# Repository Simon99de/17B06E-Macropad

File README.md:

# 17B06E-Macropad (by Simon99de)
> [!WARNING]
> Please note: The code is no longer being updated on GitHub!
> 
> The project has been moved to [Codeberg](https://codeberg.org/Simon99de/17B06E-Macropad)!

***
Eine deutsche Anleitung findest du auf meiner Website: [Simon99.de](https://simon99.de/blog/17b06e-macropad/)

It is a simple 4x4 (+1) numpad with 6 rotary encoders, 4x4 RGB LEDs, OLED display, and hot-swap keys.

You can customize all 6 encoders and 17 keys however you want. It also supports multiple layers (/pages), which means that a single key can do much more. (That's why the keyboard has 17 keys instead of 16.)

It can be an alternative to various keyboards such as Streamdeck+, Loupdeck Live, etc. if you don't need the screen behind the keys. In addition, the Macropad keyboard does not require any background software to function, which means increased compatibility.

Powered by QMK via Waveshare RP2040-Plus / Raspberry Pi Pico (1).

### What does 17B06E mean?
I chose the name 17B06E-Macropad because it describes everything the Macropad has. 17 Buttons + 6 Encoders. It also has RGB and a small OLED display.
The top button is used to switch profiles, giving you 16 x 4 (or more/less) buttons at your disposal, with the current profile shown on the display.

***

#### The old code is in the V1 branch.

#### But you should go to Codeberg! (link above)

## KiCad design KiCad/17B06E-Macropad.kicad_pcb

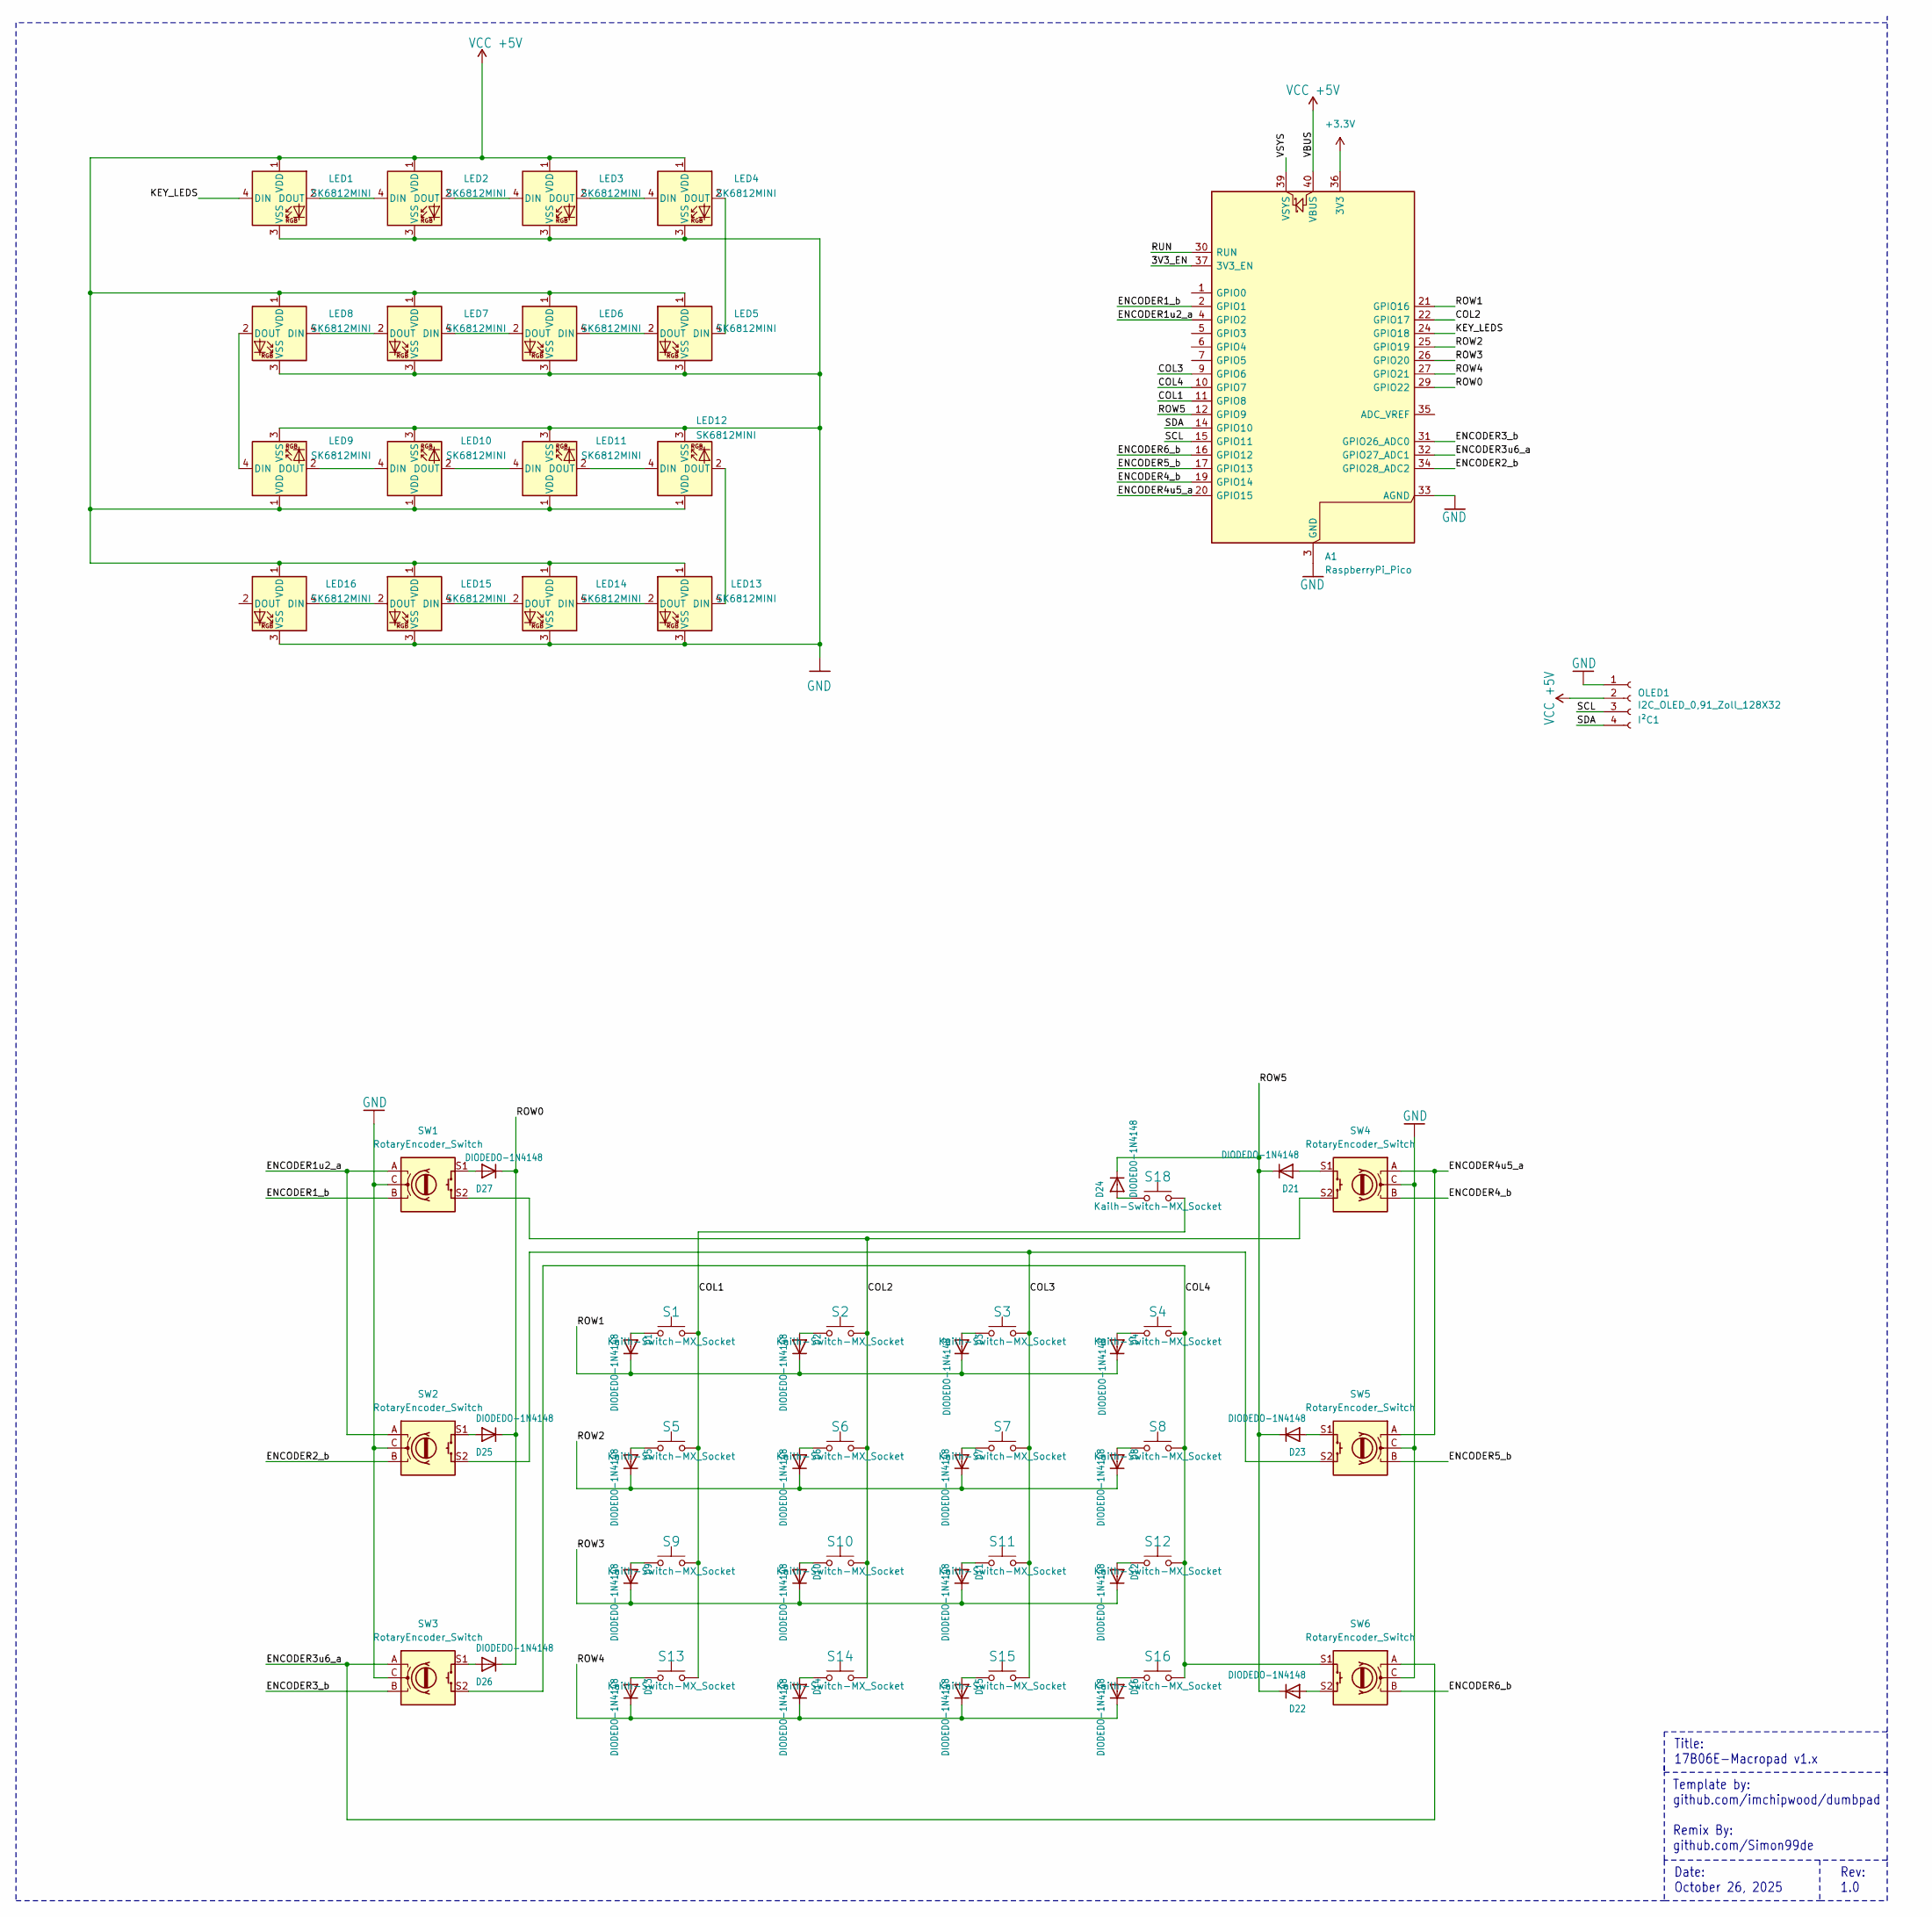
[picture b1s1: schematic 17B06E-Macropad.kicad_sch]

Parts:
A1: RaspberryPi_Pico; RaspberryPi_Pico_No_WIFI
D1, D2, D3, D4, D5, D6, D7, D8, D9, D10, D11, D12, D13, D14, D15, D16, D21, D22, D23, D24, D25, D26, D27: DIODEDO-1N4148; DO-1N4148
LED1, LED2, LED3, LED4, LED5, LED6, LED7, LED8, LED9, LED10, LED11, LED12, LED13, LED14, LED15, LED16: SK6812MINI; YS-SK6812MINI-E
OLED1: I2C_OLED_0,91_Zoll_128X32; OLED
S1, S2, S3, S4, S5, S6, S7, S8, S9, S10, S11, S12, S13, S14, S15, S16, S18: Kailh-Switch-MX_Socket; Kailh-CPG151101S11_MX_Socket-1.00u
SW1, SW2, SW3, SW4, SW5, SW6: RotaryEncoder_Switch; RotaryEncoder_Alps_EC11E-Switch_Vertical_H20mm

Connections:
/COL1: A1.11 (GPIO8), S1.2, S5.2, S9.2, S13.2, S18.2; also elsewhere on the board
/COL2: A1.22 (GPIO17), S2.2, S6.2, S10.2, S14.2, SW1.S2, SW4.S2; also elsewhere on the board
/COL3: A1.9 (GPIO6), S3.2, S7.2, S11.2, S15.2, SW2.S2, SW5.S2; also elsewhere on the board
/COL4: A1.10 (GPIO7), S4.2, S8.2, S12.2, S16.2, SW3.S2, SW6.S1; also elsewhere on the board
/ENCODER1_b: A1.2 (GPIO1), SW1.B; also elsewhere on the board
/ENCODER1u2_a: A1.4 (GPIO2), SW1.A, SW2.A; also elsewhere on the board
/ENCODER2_b: A1.34 (GPIO28_ADC2), SW2.B; also elsewhere on the board
/ENCODER3_b: A1.31 (GPIO26_ADC0), SW3.B; also elsewhere on the board
/ENCODER3u6_a: A1.32 (GPIO27_ADC1), SW3.A, SW6.A; also elsewhere on the board
/ENCODER4_b: A1.19 (GPIO14), SW4.B; also elsewhere on the board
/ENCODER4u5_a: A1.20 (GPIO15), SW4.A, SW5.A; also elsewhere on the board
/ENCODER5_b: A1.17 (GPIO13), SW5.B; also elsewhere on the board
/ENCODER6_b: A1.16 (GPIO12), SW6.B; also elsewhere on the board
/KEY_LEDS: A1.24 (GPIO18), LED1.4 (DIN); also elsewhere on the board
/ROW0: A1.29 (GPIO22), D25.C, D26.C, D27.C; also elsewhere on the board
/ROW1: A1.21 (GPIO16), D1.C, D2.C, D3.C, D4.C; also elsewhere on the board
/ROW2: A1.25 (GPIO19), D5.C, D6.C, D7.C, D8.C; also elsewhere on the board
/ROW3: A1.26 (GPIO20), D9.C, D10.C, D11.C, D12.C; also elsewhere on the board
/ROW4: A1.27 (GPIO21), D13.C, D14.C, D15.C, D16.C; also elsewhere on the board
/ROW5: A1.12 (GPIO9), D21.C, D22.C, D23.C, D24.C; also elsewhere on the board
/SCL: A1.15 (GPIO11), OLED1.3; also elsewhere on the board
/SDA: A1.14 (GPIO10), OLED1.4; also elsewhere on the board
GND: A1.3 (GND), A1.8 (GND), A1.13 (GND), A1.18 (GND), A1.23 (GND), A1.28 (GND), A1.33 (AGND), A1.38 (GND), LED1.3 (VSS), LED2.3 (VSS), LED3.3 (VSS), LED4.3 (VSS), LED5.3 (VSS), LED6.3 (VSS), LED7.3 (VSS), LED8.3 (VSS), LED9.3 (VSS), LED10.3 (VSS), LED11.3 (VSS), LED12.3 (VSS), LED13.3 (VSS), LED14.3 (VSS), LED15.3 (VSS), LED16.3 (VSS), OLED1.1, SW1.C, SW2.C, SW3.C, SW4.C, SW5.C, SW6.C; also elsewhere on the board
unnamed: D1.A, S1.1
unnamed: D2.A, S2.1
unnamed: D3.A, S3.1
unnamed: D4.A, S4.1
unnamed: D5.A, S5.1
unnamed: D6.A, S6.1
unnamed: D7.A, S7.1
unnamed: D8.A, S8.1
unnamed: D9.A, S9.1
unnamed: D10.A, S10.1
unnamed: D11.A, S11.1
unnamed: D12.A, S12.1
unnamed: D13.A, S13.1
unnamed: D14.A, S14.1
unnamed: D15.A, S15.1
unnamed: D16.A, S16.1
unnamed: D21.A, SW4.S1
unnamed: D22.A, SW6.S2
unnamed: D23.A, SW5.S1
unnamed: D24.A, S18.1
unnamed: D25.A, SW2.S1
unnamed: D26.A, SW3.S1
unnamed: D27.A, SW1.S1
unnamed: LED1.2 (DOUT), LED2.4 (DIN)
unnamed: LED2.2 (DOUT), LED3.4 (DIN)
unnamed: LED3.2 (DOUT), LED4.4 (DIN)
unnamed: LED4.2 (DOUT), LED5.4 (DIN)
unnamed: LED5.2 (DOUT), LED6.4 (DIN)
unnamed: LED6.2 (DOUT), LED7.4 (DIN)
unnamed: LED7.2 (DOUT), LED8.4 (DIN)
unnamed: LED8.2 (DOUT), LED9.4 (DIN)
unnamed: LED9.2 (DOUT), LED10.4 (DIN)
unnamed: LED10.2 (DOUT), LED11.4 (DIN)
unnamed: LED11.2 (DOUT), LED12.4 (DIN)
unnamed: LED12.2 (DOUT), LED13.4 (DIN)
unnamed: LED13.2 (DOUT), LED14.4 (DIN)
unnamed: LED14.2 (DOUT), LED15.4 (DIN)
unnamed: LED15.2 (DOUT), LED16.4 (DIN)
VCC +5V: A1.40 (VBUS), LED1.1 (VDD), LED2.1 (VDD), LED3.1 (VDD), LED4.1 (VDD), LED5.1 (VDD), LED6.1 (VDD), LED7.1 (VDD), LED8.1 (VDD), LED9.1 (VDD), LED10.1 (VDD), LED11.1 (VDD), LED12.1 (VDD), LED13.1 (VDD), LED14.1 (VDD), LED15.1 (VDD), LED16.1 (VDD), OLED1.2; also elsewhere on the board

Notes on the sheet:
Rev: 1.0
Template by: github.com/imchipwood/dumbpad Remix By: github.com/Simon99de
Title: 17B06E-Macropad v1.x
Date: October 26, 2025

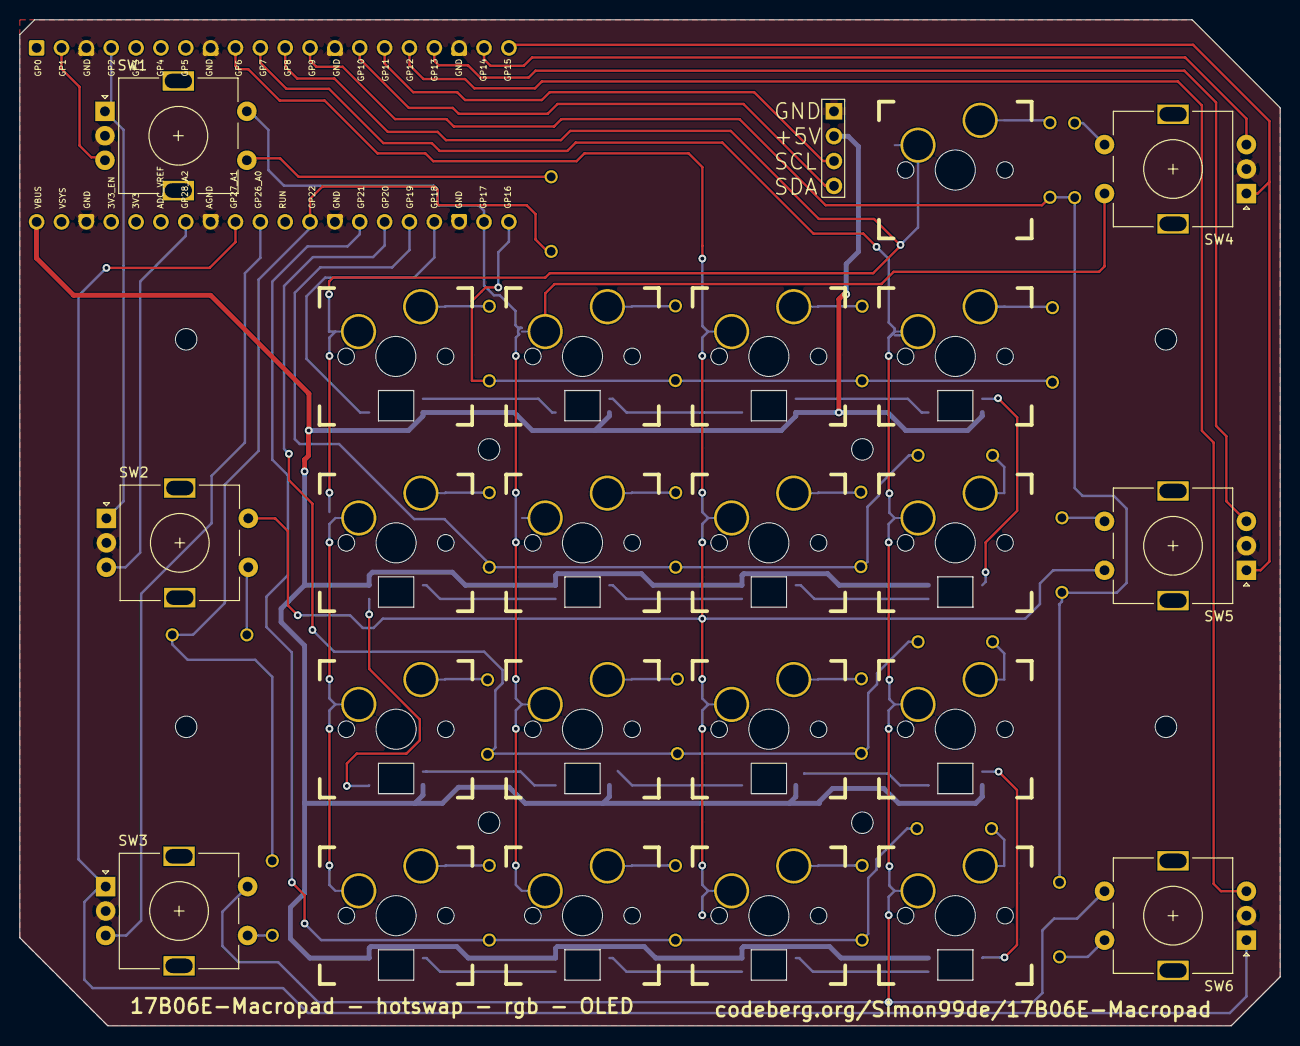
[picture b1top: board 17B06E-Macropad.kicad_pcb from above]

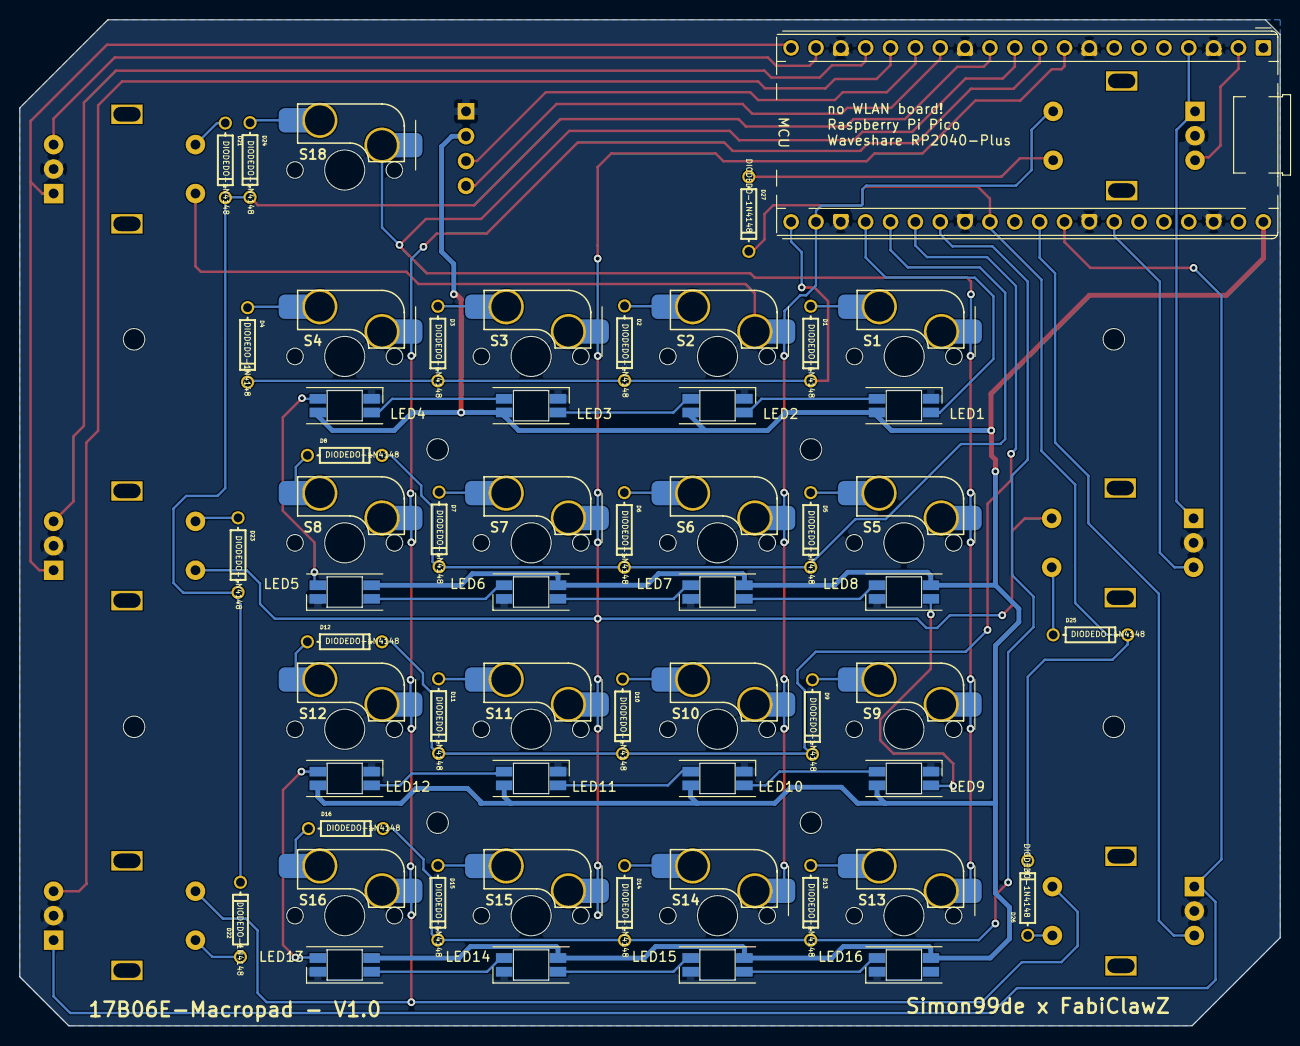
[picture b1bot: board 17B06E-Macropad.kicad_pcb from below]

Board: 2 copper layers, 128.7 x 102.7 mm, 64 parts (57 on the bottom side), 62 nets.

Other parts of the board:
MCU: RaspberryPi_Pico; RaspberryPi_Pico_No_WIFI

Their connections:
/COL1: MCU.11 (GPIO8); also elsewhere on the board
/COL2: MCU.22 (GPIO17); also elsewhere on the board
/COL3: MCU.9 (GPIO6); also elsewhere on the board
/COL4: MCU.10 (GPIO7); also elsewhere on the board
/ENCODER1_b: MCU.2 (GPIO1); also elsewhere on the board
/ENCODER1u2_a: MCU.4 (GPIO2); also elsewhere on the board
/ENCODER2_b: MCU.34 (GPIO28_ADC2); also elsewhere on the board
/ENCODER3_b: MCU.31 (GPIO26_ADC0); also elsewhere on the board
/ENCODER3u6_a: MCU.32 (GPIO27_ADC1); also elsewhere on the board
/ENCODER4_b: MCU.19 (GPIO14); also elsewhere on the board
/ENCODER4u5_a: MCU.20 (GPIO15); also elsewhere on the board
/ENCODER5_b: MCU.17 (GPIO13); also elsewhere on the board
/ENCODER6_b: MCU.16 (GPIO12); also elsewhere on the board
/KEY_LEDS: MCU.24 (GPIO18); also elsewhere on the board
/ROW0: MCU.29 (GPIO22); also elsewhere on the board
/ROW1: MCU.21 (GPIO16); also elsewhere on the board
/ROW2: MCU.25 (GPIO19); also elsewhere on the board
/ROW3: MCU.26 (GPIO20); also elsewhere on the board
/ROW4: MCU.27 (GPIO21); also elsewhere on the board
/ROW5: MCU.12 (GPIO9); also elsewhere on the board
/SCL: MCU.15 (GPIO11); also elsewhere on the board
/SDA: MCU.14 (GPIO10); also elsewhere on the board
GND: MCU.3 (GND), MCU.8 (GND), MCU.13 (GND), MCU.18 (GND), MCU.23 (GND), MCU.28 (GND), MCU.33 (AGND), MCU.38 (GND); also elsewhere on the board
VCC +5V: MCU.40 (VBUS); also elsewhere on the board

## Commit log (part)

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2025-10-26 PCB layout KiCad data
2025-10-30 Various adjustments/improvements
2025-10-30 Encoder better labeled as a/b in the schematic
2025-10-31 Update README.md
    more description text added
2025-11-01 various changes
    holes changed,
    schematic correctly arranged,
    and even more
2025-11-01 Delete KiCad/17B06E-Macropad.pretty/LED_3MM.kicad_mod
    is not needed/is too much
2025-11-01 Delete KiCad/17B06E-Macropad.pretty/AXIAL-0.3.kicad_mod
    is not needed/is too much
2025-11-01 Delete KiCad/17B06E-Macropad.pretty/TACTILE_SWITCH_PTH_6.0MM.kicad_mod
    is not needed/is too much
2025-11-01 Pin description added for MCU
2025-11-01 PCB manufactures Data
2025-11-09 Preparation for upload
    The folders are still empty. This is preparation for the upload, so that there will be less stress when the time comes.
2025-11-09 Update README.md
    More information added and prepared for links to be inserted.
2025-11-10 Update README.md
    added note
2025-11-11 Update rgb mounting
2025-11-16 V1.0
2025-11-16 Delete 17B06E-Macropad_gerber.zip
    alpha data
2025-11-16 Update README.md
    forgot the screws for the housing
2025-11-17 Update README.md
    Thanks FabiClawZ for the suggestions for improvement :)
2025-11-17 Update README.md
    Added info about problems
2025-11-17 add entcoder matrix
2025-11-17 Update
    encoder matrix image added + example
2025-11-17 Update
    rubber buffer added
2025-11-21 stl + 3mf file uploaded
    stl + 3mf file uploaded for testing, prior to release.
2025-11-21 add photos
2025-11-21 Update README.md
    images added
2025-11-21 Update Gallery
    images arranged more compactly
2025-11-21 add oled +led picture
2025-11-21 add oled + led Picture
2025-11-21 images adapted with QR code + link
2025-11-22 Update README.md
    factory reset added
2025-11-22 test files!
2025-11-28 update
    slightly enlarged to ensure a better fit
2025-11-28 README: beta firmware
    beta firmware info added
2025-11-28 Beta!!! Firmware added (buggy)
    This firmware should only be used for testing purposes, as it is not yet complete!
2025-11-28 Update README.md
    preparation for pictures
2025-11-30 Update README.md
    What is 10b06e? More information added.
2025-11-30 Update README.md
    What is 10b06e, more information added, space added, improved readability
2025-11-30 images reduced in size
    images slightly reduced in size for faster page loading times
2025-11-30 Update README.md
    German instructions added.
    (on my website)
2025-11-30 Update README.md
    update url
2025-11-30 Optional scripts added
2025-11-30 Update README.md
    Information added to scripts
2025-12-03 Update README.md
    Add By simon99de
2025-12-04 Update README.md
    OLED display changed from optional to recommended
2025-12-05 Update README.md
    added what I did to the project Simon99de
2025-12-07 Update issue templates
2025-12-13 Update README.md
    add space
2025-12-21 Update README.md
    picture add: hotswap-MCU
2025-12-21 add images
    add hotswap MCU housing images
2025-12-21 Update README.md
    add mods
2025-12-21 Update README.md
    add mods info
2025-12-21 alignment changed
2025-12-21 Update README.md
    links to printables etc. adjusted
2026-03-14 Rename store-buy-kits.md to buy_kits.md
2026-03-14 Update README.md
    Add Store / Kit Infos to buy / sell
2026-05-30 Update README.md
    Adjusted, since the QMK website / via isn't working yet. Preparing for a release without Via support; that's what Vial is for.
2026-05-30 Update README.md
    add firmware url source
2026-05-30 Update README.md
    URL source updated
2026-05-31 Update README.md
    Reset url updated
2026-06-05 Firmware-Update veröffentlichen
2026-06-05 Delete firmware/beta-simon99de_17b06e_rgb_vial.uf2
    Removed because it is an unstable beta version
2026-06-05 add vial-qmk URL code
2026-06-05 Update README.md
    Added a link to the geber source file
2026-06-06 Update README.md
    I've made various changes to things that were incorrect or had been overlooked.
